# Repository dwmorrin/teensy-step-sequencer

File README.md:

# Teensy Step Sequencer

This project implements a hardware-based step sequencer using the Teensy 4.1 microcontroller. It utilizes the Teensy's onboard USB Host capabilities to accept input from standard USB keyboards, alongside a custom 32-switch diode matrix for tactile control.

## Gallery

### Version 1 first build

### Prototype

### Hardware Renders

|                         Main Board                         |                         Switchplate                         |
| :-----------------------------------------------------: | :-------------------------------------------------------: |
|  |  |

## System Overview

The application is designed as a standalone, embedded instrument. It functions as an **8-track** step sequencer with support for **96 PPQN high-resolution timing**, pattern chaining (Song Mode), **per-track swing**, real-time performance triggers, and visual feedback via an I2C OLED display with scrolling track views.

### Hardware Dependencies

- **Microcontroller:** Teensy 4.1 (Selected for native USB Host and RAM capacity).
- **Display:** - 1.3" SH1106 OLED (I2C) for the graphical interface.
  - 16x LEDs driven by 74HC595 Shift Registers for step visualization.
- **Input:** - Standard USB HID Keyboard (via USB Host).
  - 4x8 Diode Matrix Keyboard (32 switches).
  - 2x Analog Potentiometers (Tempo and Parameter control).
- **Output:** **8x** 5V Logic Triggers (GPIO).

## Software Architecture

The codebase adopts a modular architecture separating data, presentation, and hardware control. The source code located in `src/` is organized into the following domains:

- **Model** (`src/Model/`)
  This directory contains the core logic and data structures. It serves as the single source of truth for the application, managing the Pattern Pool, the Playlist (Song Mode), Swing parameters, and the Undo buffer. The Model is decoupled from hardware; it does not know if it is being driven by a clock or edited by a keyboard.

- **View** (`src/View/`)
  This directory handles all visual output.
  - `DisplayManager`: Observes the Model and renders the interface (Grid, Transport, Headers) to the OLED. It handles **viewport scrolling** to display 8 tracks on a 4-track height screen.
  - `StepLeds`: Manages the 16-step LED array via SPI shift registers.
    The view layer includes internal throttling logic to maintain a consistent frame rate without blocking the audio/timing threads.

- **Controller** (`src/Controller/`)
  This directory manages user input and state routing. The `UIManager` aggregates inputs from multiple hardware sources:
  - **USB Keyboard:** Handled via the Teensy USBHost_t36 library.
  - **Matrix:** Handled by `KeyMatrix`, a custom driver for scanning the 4x8 diode array.
  - **Analog:** Handled by `AnalogInput`, which provides hysteresis and signal smoothing for potentiometers.

  Inputs are translated into abstract `InputCommands` (e.g., `CMD_TRANSPORT_TOGGLE`), decoupling the physical control method from the internal application logic.

- **Engine** (`src/Engine/`)
  This directory handles real-time operations.
  - `ClockEngine`: A **96 PPQN** (Pulses Per Quarter Note) interrupt-driven engine. It calculates micro-timing for **Swing** and groove effects, offering 24 "ticks" per 16th-note step.
  - `OutputDriver`: Abstraction layer for the physical hardware. It converts track bitmasks into GPIO signals using high-precision interrupt timers.

- **Configuration** (`src/Config.h`)
  A global header file defining build-time constraints, including track count, pattern limits, pin mappings, and signal polarity.

## Expansion Guidelines

The system is designed to be extensible. Developers looking to expand functionality should consider the following architectural patterns:

### Persistence (SD Card Storage)

Current pattern data is stored in volatile RAM and is lost upon power cycle. The Teensy 4.1 includes a native micro-SD card slot. Future development should implement a `PersistenceManager` class. This component should:

1.  Serialize the `SequencerModel` data structures (Pattern Pool and Playlist) into a binary or JSON format.
2.  Write to the SD card using the standard Arduino SD library.
3.  Interface with the `UIManager` to allow loading and saving of projects.

## Timing Calculation

The system timing is based on a standard 4/4 time signature where a "beat" represents a quarter note. 

The engine runs at **96 PPQN** resolution. The interval $T$ (milliseconds per tick) is calculated as:

$$T = \frac{60,000}{BPM \times 96}$$

For a standard trigger pulse width of 15ms, the system manages overlapping triggers via a pulse-counter in the interrupt service routine.

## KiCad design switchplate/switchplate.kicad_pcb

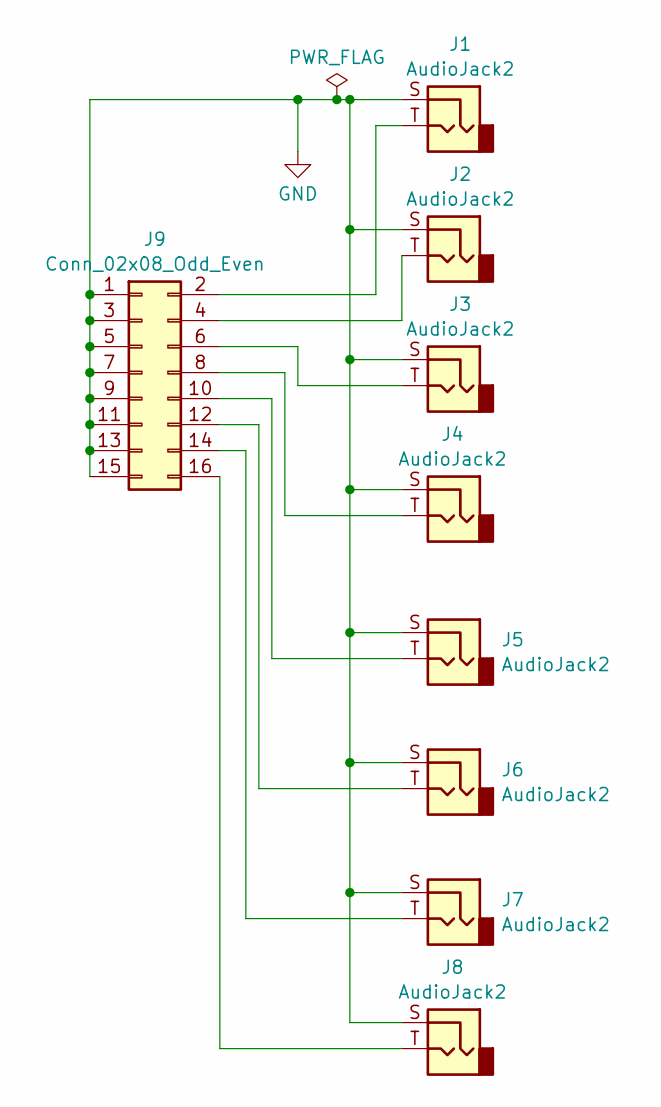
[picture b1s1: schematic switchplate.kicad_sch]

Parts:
J1, J2, J3, J4, J5, J6, J7, J8: AudioJack2; Jack_3.5mm_CUI_SJ1-3523N_Horizontal; MPN SJ1-3523N
J9: Conn_02x08_Odd_Even; PinHeader_2x08_P2.54mm_Vertical; MPN TSW-108-14-T-D

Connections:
GND: J1.S, J2.S, J3.S, J4.S, J5.S, J6.S, J7.S, J8.S, J9.1, J9.3, J9.5, J9.7, J9.9, J9.11, J9.13, J9.15
unnamed: J1.T, J9.2
unnamed: J2.T, J9.4
unnamed: J3.T, J9.6
unnamed: J4.T, J9.8
unnamed: J5.T, J9.10
unnamed: J6.T, J9.12
unnamed: J7.T, J9.14
unnamed: J8.T, J9.16

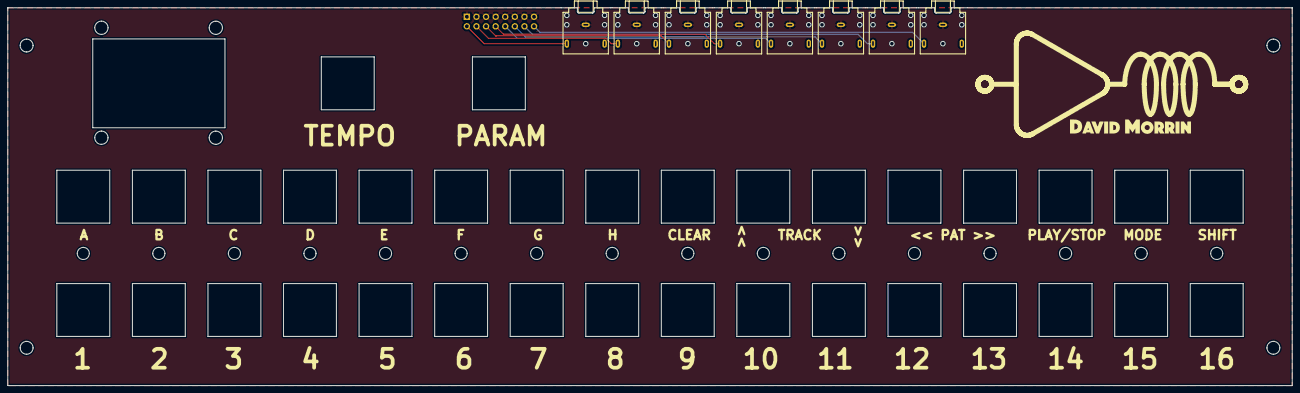
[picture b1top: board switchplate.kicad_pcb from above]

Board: 2 copper layers, 340.0 x 100.0 mm, 9 parts (1 on the bottom side), 9 nets.

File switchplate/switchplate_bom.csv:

Reference	Qty	Value	DNP	Exclude from BOM	Exclude from Board	Footprint	Datasheet	MPN
J1,J2,J3,J4,J5,J6,J7,J8	8	AudioJack2				Connector_Audio:Jack_3.5mm_CUI_SJ1-3523N_Horizontal	https://www.mouser.com/datasheet/3/6118/1/sj1_352xn.pdf	SJ1-3523N
J9	1	Conn_02x08_Odd_Even				Connector_PinHeader_2.54mm:PinHeader_2x08_P2.54mm_Vertical	https://suddendocs.samtec.com/productspecs/tsw-sxx.pdf	TSW-108-14-T-D

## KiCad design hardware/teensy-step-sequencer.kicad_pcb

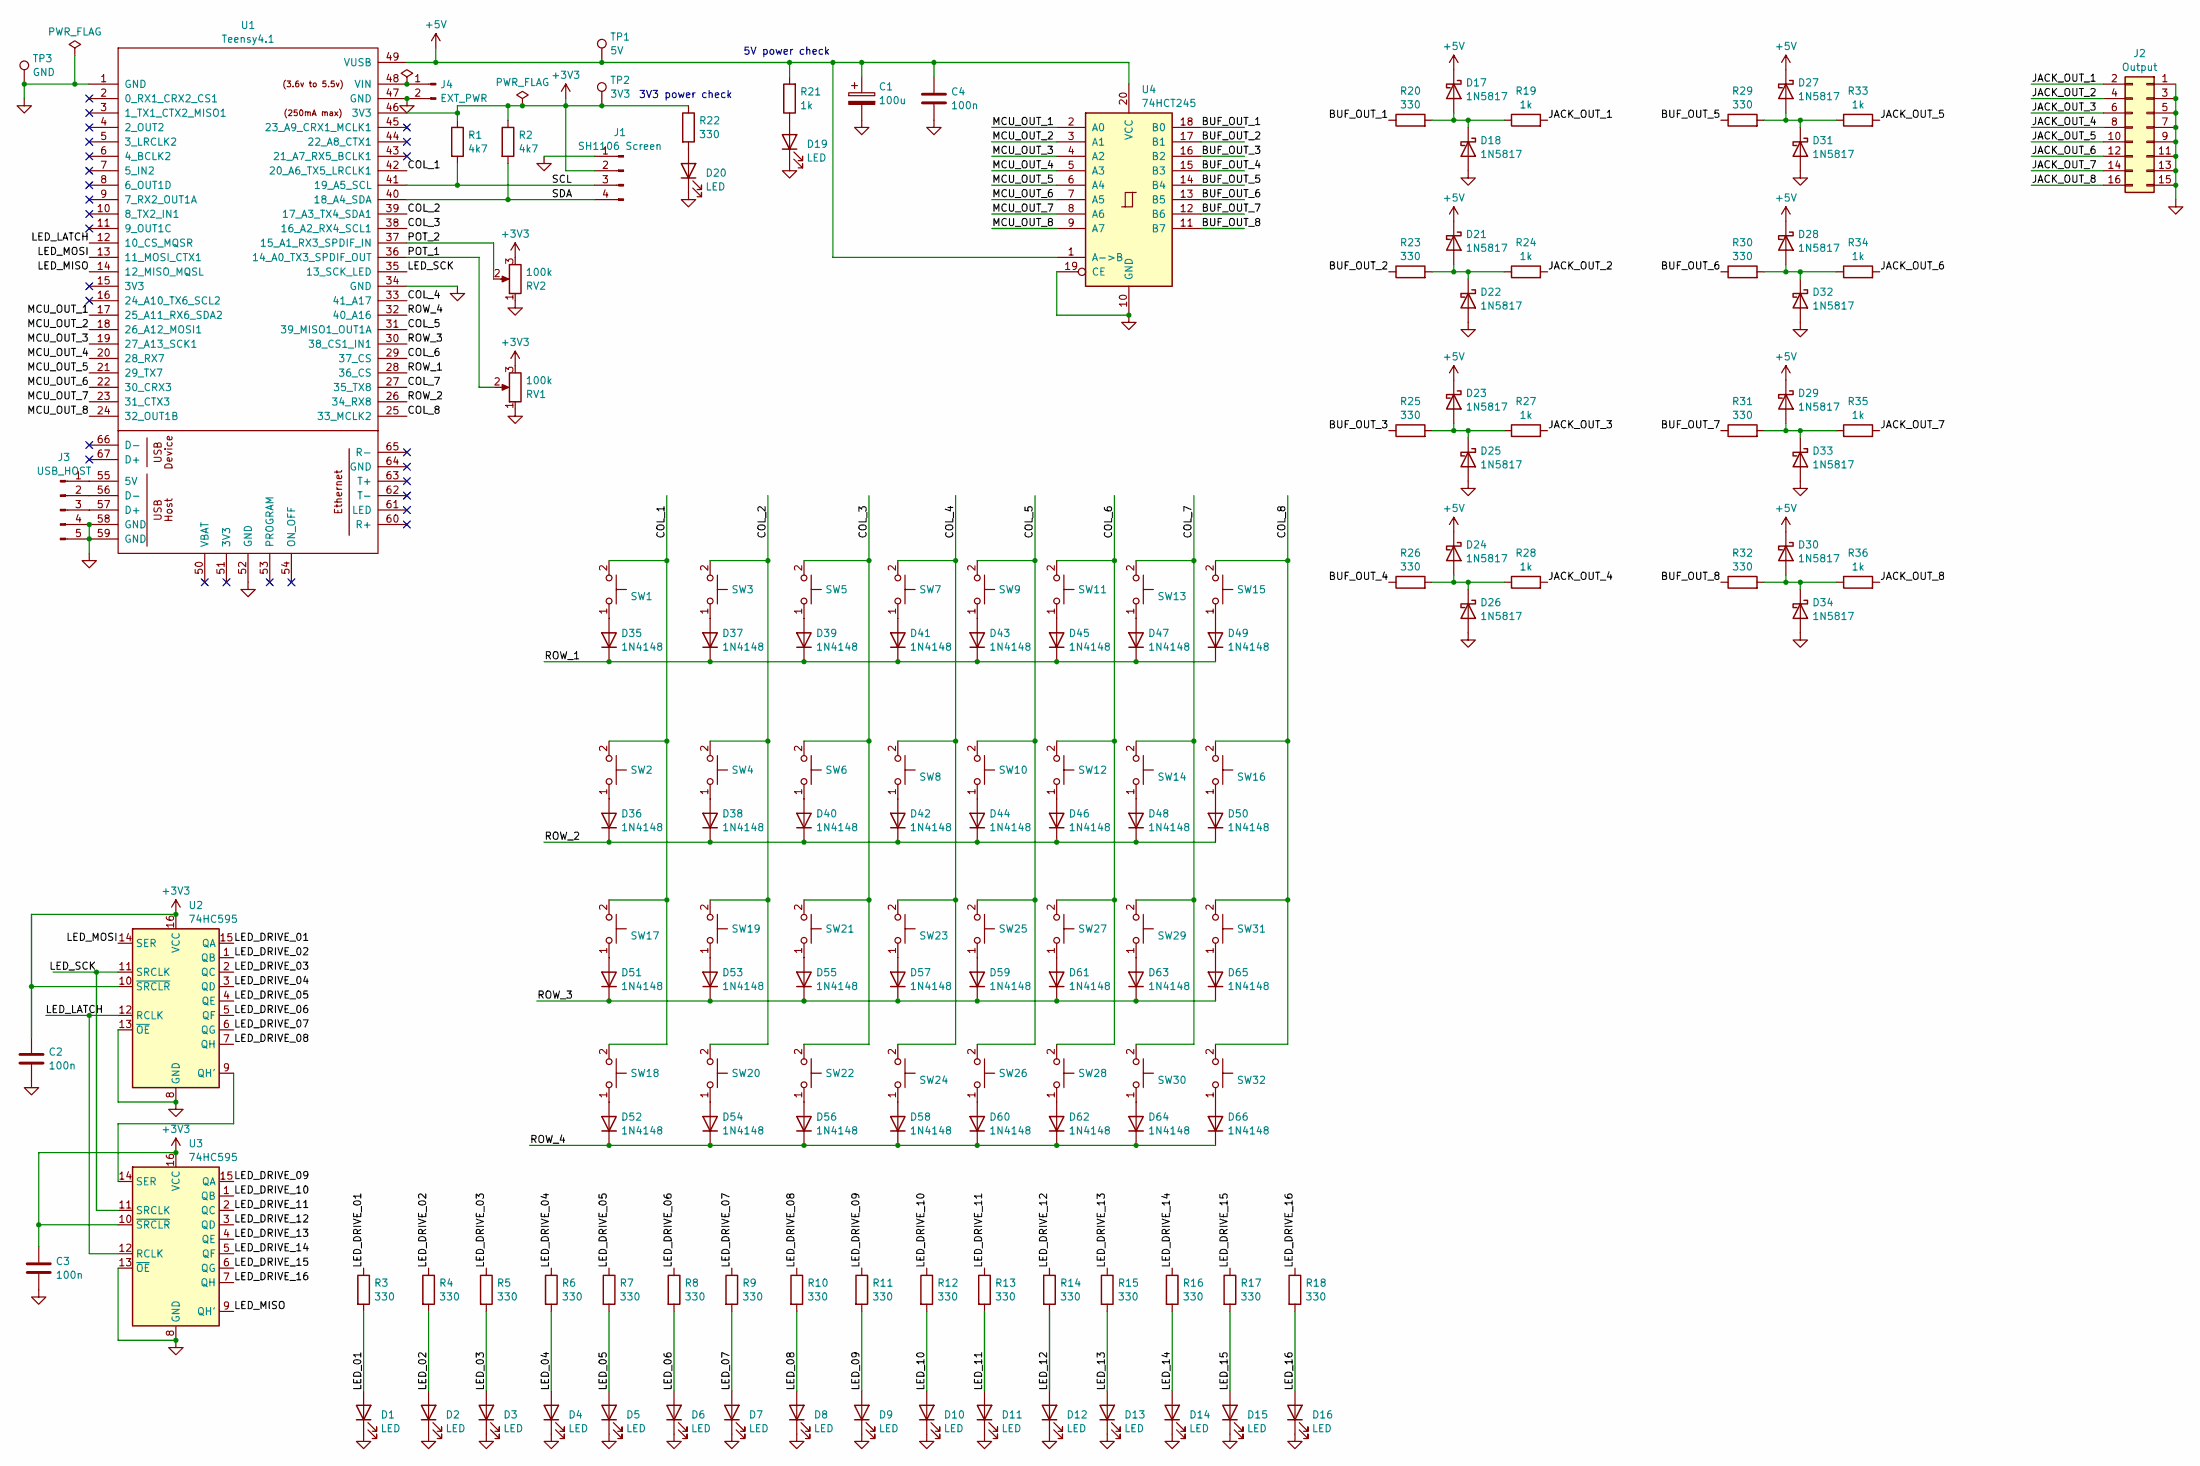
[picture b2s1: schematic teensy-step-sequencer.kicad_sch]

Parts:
C1: 100u; CP_Radial_D5.0mm_P2.50mm
C2, C3, C4: 100n; C_Disc_D5.0mm_W2.5mm_P2.50mm
D1, D2, D3, D4, D5, D6, D7, D8, D9, D10, D11, D12, D13, D14, D15, D16, D19, D20: LED; LED_D3.0mm
D17, D18, D21, D22, D23, D24, D25, D26, D27, D28, D29, D30, D31, D32, D33, D34: 1N5817; D_DO-15_P10.16mm_Horizontal
D35, D36, D37, D38, D39, D40, D41, D42, D43, D44, D45, D46, D47, D48, D49, D50, D51, D52, D53, D54, D55, D56, D57, D58, D59, D60, D61, D62, D63, D64, D65, D66: 1N4148; D_DO-35_SOD27_P7.62mm_Horizontal
J1: SH1106 Screen; PinHeader_1x04_P2.54mm_Vertical
J2: Output; PinHeader_2x08_P2.54mm_Vertical
J3: USB_HOST; PinHeader_1x05_P2.54mm_Vertical
J4: EXT_PWR; PinHeader_1x02_P2.54mm_Vertical
R1, R2: 4k7; R_Axial_DIN0207_L6.3mm_D2.5mm_P10.16mm_Horizontal
R3, R4, R5, R6, R7, R8, R9, R10, R11, R12, R13, R14, R15, R16, R17, R18, R20, R22, R23, R25, R26, R29, R30, R31, R32: 330; R_Axial_DIN0207_L6.3mm_D2.5mm_P10.16mm_Horizontal
R19, R21, R24, R27, R28, R33, R34, R35, R36: 1k; R_Axial_DIN0207_L6.3mm_D2.5mm_P10.16mm_Horizontal
RV1, RV2: 100k; Potentiometer_Bourns_PTV09A-1_Single_Vertical
SW1, SW2, SW3, SW4, SW5, SW6, SW7, SW8, SW9, SW10, SW11, SW12, SW13, SW14, SW15, SW16, SW17, SW18, SW19, SW20, SW21, SW22, SW23, SW24, SW25, SW26, SW27, SW28, SW29, SW30, SW31, SW32: CherryMX; CherryMX_1.00u
TP1: 5V; TestPoint_Keystone_5000-5004_Miniature
TP2: 3V3; TestPoint_Keystone_5000-5004_Miniature
TP3: GND; TestPoint_Keystone_5000-5004_Miniature
U1: Teensy4.1; Teensy41
U2, U3: 74HC595; DIP-16_W7.62mm
U4: 74HCT245; DIP-20_W7.62mm

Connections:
+3V3: C2.1, C3.1, J1.2, R1.1, R2.1, R22.1, RV1.3, RV2.3, TP2.1, U1.46 (3V3), U2.10 (~SRCLR), U2.16 (VCC), U3.10 (~SRCLR), U3.16 (VCC)
+5V: C1.1, C4.1, D17.1 (K), D21.1 (K), D23.1 (K), D24.1 (K), D27.1 (K), D28.1 (K), D29.1 (K), D30.1 (K), R21.2, TP1.1, U1.49 (VUSB), U4.1 (A->B), U4.20 (VCC)
/BUF_OUT_1: R20.1, U4.18 (B0)
/BUF_OUT_2: R23.1, U4.17 (B1)
/BUF_OUT_3: R25.1, U4.16 (B2)
/BUF_OUT_4: R26.1, U4.15 (B3)
/BUF_OUT_5: R29.1, U4.14 (B4)
/BUF_OUT_6: R30.1, U4.13 (B5)
/BUF_OUT_7: R31.1, U4.12 (B6)
/BUF_OUT_8: R32.1, U4.11 (B7)
/COL_1: SW1.2, SW2.2, SW17.2, SW18.2, U1.42 (20_A6_TX5_LRCLK1)
/COL_2: SW3.2, SW4.2, SW19.2, SW20.2, U1.39 (17_A3_TX4_SDA1)
/COL_3: SW5.2, SW6.2, SW21.2, SW22.2, U1.38 (16_A2_RX4_SCL1)
/COL_4: SW7.2, SW8.2, SW23.2, SW24.2, U1.33 (41_A17)
/COL_5: SW9.2, SW10.2, SW25.2, SW26.2, U1.31 (39_MISO1_OUT1A)
/COL_6: SW11.2, SW12.2, SW27.2, SW28.2, U1.29 (37_CS)
/COL_7: SW13.2, SW14.2, SW29.2, SW30.2, U1.27 (35_TX8)
/COL_8: SW15.2, SW16.2, SW31.2, SW32.2, U1.25 (33_MCLK2)
/JACK_OUT_1: J2.2, R19.2
/JACK_OUT_2: J2.4, R24.2
/JACK_OUT_3: J2.6, R27.2
/JACK_OUT_4: J2.8, R28.2
/JACK_OUT_5: J2.10, R33.2
/JACK_OUT_6: J2.12, R34.2
/JACK_OUT_7: J2.14, R35.2
/JACK_OUT_8: J2.16, R36.2
/LED_01: D1.2 (A), R3.2
/LED_02: D2.2 (A), R4.2
/LED_03: D3.2 (A), R5.2
/LED_04: D4.2 (A), R6.2
/LED_05: D5.2 (A), R7.2
/LED_06: D6.2 (A), R8.2
/LED_07: D7.2 (A), R9.2
/LED_08: D8.2 (A), R10.2
/LED_09: D9.2 (A), R11.2
/LED_10: D10.2 (A), R12.2
/LED_11: D11.2 (A), R13.2
/LED_12: D12.2 (A), R14.2
/LED_13: D13.2 (A), R15.2
/LED_14: D14.2 (A), R16.2
/LED_15: D15.2 (A), R17.2
/LED_16: D16.2 (A), R18.2
/LED_DRIVE_01: R3.1, U2.15 (QA)
/LED_DRIVE_02: R4.1, U2.1 (QB)
/LED_DRIVE_03: R5.1, U2.2 (QC)
/LED_DRIVE_04: R6.1, U2.3 (QD)
/LED_DRIVE_05: R7.1, U2.4 (QE)
/LED_DRIVE_06: R8.1, U2.5 (QF)
/LED_DRIVE_07: R9.1, U2.6 (QG)
/LED_DRIVE_08: R10.1, U2.7 (QH)
/LED_DRIVE_09: R11.1, U3.15 (QA)
/LED_DRIVE_10: R12.1, U3.1 (QB)
/LED_DRIVE_11: R13.1, U3.2 (QC)
/LED_DRIVE_12: R14.1, U3.3 (QD)
/LED_DRIVE_13: R15.1, U3.4 (QE)
/LED_DRIVE_14: R16.1, U3.5 (QF)
/LED_DRIVE_15: R17.1, U3.6 (QG)
/LED_DRIVE_16: R18.1, U3.7 (QH)
/LED_LATCH: U1.12 (10_CS_MQSR), U2.12 (RCLK), U3.12 (RCLK)
/LED_MISO: U1.14 (12_MISO_MQSL), U3.9 (QH')
/LED_MOSI: U1.13 (11_MOSI_CTX1), U2.14 (SER)
/LED_SCK: U1.35 (13_SCK_LED), U2.11 (SRCLK), U3.11 (SRCLK)
/MCU_OUT_1: U1.17 (25_A11_RX6_SDA2), U4.2 (A0)
/MCU_OUT_2: U1.18 (26_A12_MOSI1), U4.3 (A1)
/MCU_OUT_3: U1.19 (27_A13_SCK1), U4.4 (A2)
/MCU_OUT_4: U1.20 (28_RX7), U4.5 (A3)
/MCU_OUT_5: U1.21 (29_TX7), U4.6 (A4)
/MCU_OUT_6: U1.22 (30_CRX3), U4.7 (A5)
/MCU_OUT_7: U1.23 (31_CTX3), U4.8 (A6)
/MCU_OUT_8: U1.24 (32_OUT1B), U4.9 (A7)
/POT_1: RV1.2, U1.36 (14_A0_TX3_SPDIF_OUT)
/POT_2: RV2.2, U1.37 (15_A1_RX3_SPDIF_IN)
/ROW_1: D35.1 (K), D37.1 (K), D39.1 (K), D41.1 (K), D43.1 (K), D45.1 (K), D47.1 (K), D49.1 (K), U1.28 (36_CS)
/ROW_2: D36.1 (K), D38.1 (K), D40.1 (K), D42.1 (K), D44.1 (K), D46.1 (K), D48.1 (K), D50.1 (K), U1.26 (34_RX8)
/ROW_3: D51.1 (K), D53.1 (K), D55.1 (K), D57.1 (K), D59.1 (K), D61.1 (K), D63.1 (K), D65.1 (K), U1.30 (38_CS1_IN1)
/ROW_4: D52.1 (K), D54.1 (K), D56.1 (K), D58.1 (K), D60.1 (K), D62.1 (K), D64.1 (K), D66.1 (K), U1.32 (40_A16)
/SCL: J1.3, R1.2, U1.41 (19_A5_SCL)
/SDA: J1.4, R2.2, U1.40 (18_A4_SDA)
GND: C1.2, C2.2, C3.2, C4.2, D1.1 (K), D2.1 (K), D3.1 (K), D4.1 (K), D5.1 (K), D6.1 (K), D7.1 (K), D8.1 (K), D9.1 (K), D10.1 (K), D11.1 (K), D12.1 (K), D13.1 (K), D14.1 (K), D15.1 (K), D16.1 (K), D18.2 (A), D19.1 (K), D20.1 (K), D22.2 (A), D25.2 (A), D26.2 (A), D31.2 (A), D32.2 (A), D33.2 (A), D34.2 (A), J1.1, J2.1, J2.3, J2.5, J2.7, J2.9, J2.11, J2.13, J2.15, J3.4, J3.5, J4.2, RV1.1, RV2.1, TP3.1, U1.1 (GND), U1.34 (GND), U1.47 (GND), U1.52 (GND), U1.58 (GND), U1.59 (GND), U2.8 (GND), U2.13 (~OE), U3.8 (GND), U3.13 (~OE), U4.10 (GND), U4.19 (CE)
unnamed: D17.2 (A), D18.1 (K), R19.1, R20.2
unnamed: D19.2 (A), R21.1
unnamed: D20.2 (A), R22.2
unnamed: D21.2 (A), D22.1 (K), R23.2, R24.1
unnamed: D23.2 (A), D25.1 (K), R25.2, R27.1
unnamed: D24.2 (A), D26.1 (K), R26.2, R28.1
unnamed: D27.2 (A), D31.1 (K), R29.2, R33.1
unnamed: D28.2 (A), D32.1 (K), R30.2, R34.1
unnamed: D29.2 (A), D33.1 (K), R31.2, R35.1
unnamed: D30.2 (A), D34.1 (K), R32.2, R36.1
unnamed: D35.2 (A), SW1.1
unnamed: D36.2 (A), SW2.1
unnamed: D37.2 (A), SW3.1
unnamed: D38.2 (A), SW4.1
unnamed: D39.2 (A), SW5.1
unnamed: D40.2 (A), SW6.1
unnamed: D41.2 (A), SW7.1
unnamed: D42.2 (A), SW8.1
unnamed: D43.2 (A), SW9.1
unnamed: D44.2 (A), SW10.1
unnamed: D45.2 (A), SW11.1
unnamed: D46.2 (A), SW12.1
unnamed: D47.2 (A), SW13.1
unnamed: D48.2 (A), SW14.1
unnamed: D49.2 (A), SW15.1
unnamed: D50.2 (A), SW16.1
unnamed: D51.2 (A), SW17.1
unnamed: D52.2 (A), SW18.1
unnamed: D53.2 (A), SW19.1
unnamed: D54.2 (A), SW20.1
unnamed: D55.2 (A), SW21.1
unnamed: D56.2 (A), SW22.1
unnamed: D57.2 (A), SW23.1
unnamed: D58.2 (A), SW24.1
unnamed: D59.2 (A), SW25.1
unnamed: D60.2 (A), SW26.1
unnamed: D61.2 (A), SW27.1
unnamed: D62.2 (A), SW28.1
unnamed: D63.2 (A), SW29.1
unnamed: D64.2 (A), SW30.1
unnamed: D65.2 (A), SW31.1
unnamed: D66.2 (A), SW32.1
unnamed: J3.1, U1.55 (5V)
unnamed: J3.2, U1.56 (D-)
unnamed: J3.3, U1.57 (D+)
unnamed: J4.1, U1.48 (VIN)
unnamed: U2.9 (QH'), U3.14 (SER)

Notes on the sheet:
5V power check
3V3 power check

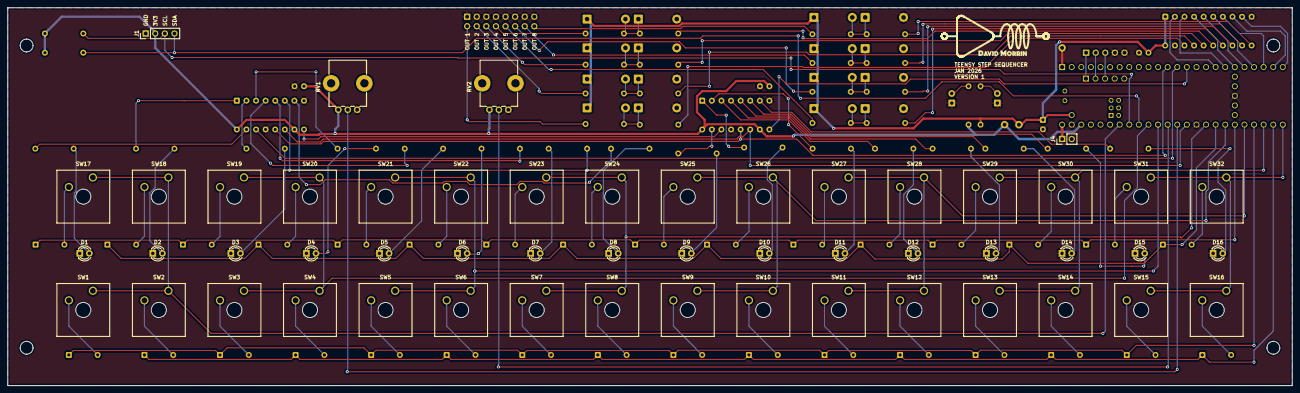
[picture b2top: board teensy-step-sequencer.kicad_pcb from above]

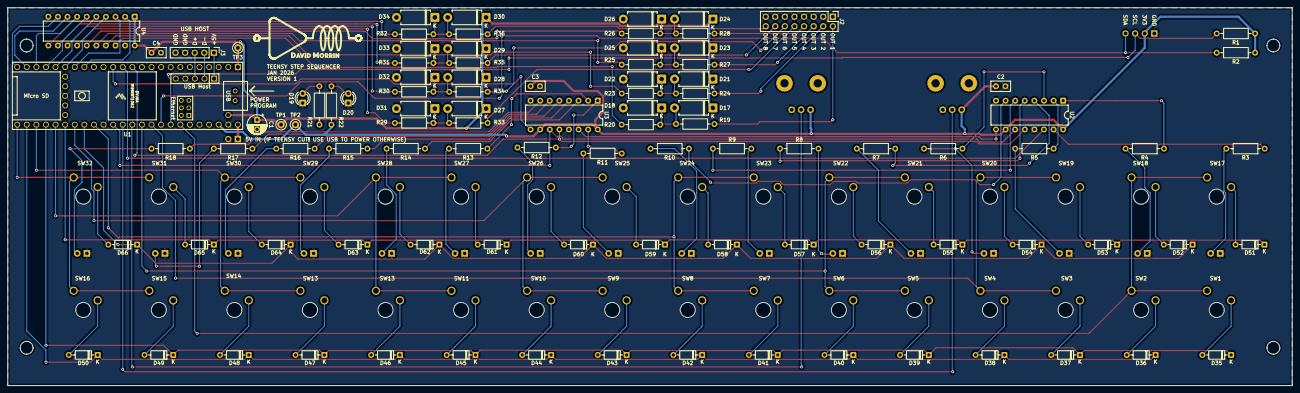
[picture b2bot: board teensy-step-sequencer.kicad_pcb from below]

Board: 2 copper layers, 340.0 x 100.0 mm, 151 parts (99 on the bottom side), 126 nets.

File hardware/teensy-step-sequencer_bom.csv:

Reference	Qty	Value	DNP	Exclude from BOM	Exclude from Board	Footprint	Datasheet
C1	1	100u				Capacitor_THT:CP_Radial_D5.0mm_P2.50mm	~
C2,C3,C4	3	100n				Capacitor_THT:C_Disc_D5.0mm_W2.5mm_P2.50mm	~
D1,D2,D3,D4,D5,D6,D7,D8,D9,D10,D11,D12,D13,D14,D15,D16,D19,D20	18	LED				LED_THT:LED_D3.0mm	~
D17,D18,D21,D22,D23,D24,D25,D26,D27,D28,D29,D30,D31,D32,D33,D34	16	1N5817				Diode_THT:D_DO-15_P10.16mm_Horizontal	http://www.vishay.com/docs/88525/1n5817.pdf
D35,D36,D37,D38,D39,D40,D41,D42,D43,D44,D45,D46,D47,D48,D49,D50,D51,D52,D53,D54,D55,D56,D57,D58,D59,D60,D61,D62,D63,D64,D65,D66	32	1N4148				Diode_THT:D_DO-35_SOD27_P7.62mm_Horizontal	~
J1	1	SH1106 Screen				Connector_PinHeader_2.54mm:PinHeader_1x04_P2.54mm_Vertical	~
J2	1	Output				Connector_PinHeader_2.54mm:PinHeader_2x08_P2.54mm_Vertical	~
J3	1	USB_HOST				Connector_PinHeader_2.54mm:PinHeader_1x05_P2.54mm_Vertical	~
J4	1	EXT_PWR				Connector_PinHeader_2.54mm:PinHeader_1x02_P2.54mm_Vertical	~
R1,R2	2	4k7				Resistor_THT:R_Axial_DIN0207_L6.3mm_D2.5mm_P10.16mm_Horizontal	~
R3,R4,R5,R6,R7,R8,R9,R10,R11,R12,R13,R14,R15,R16,R17,R18,R20,R22,R23,R25,R26,R29,R30,R31,R32	25	330				Resistor_THT:R_Axial_DIN0207_L6.3mm_D2.5mm_P10.16mm_Horizontal	~
R19,R21,R24,R27,R28,R33,R34,R35,R36	9	1k				Resistor_THT:R_Axial_DIN0207_L6.3mm_D2.5mm_P10.16mm_Horizontal	~
RV1,RV2	2	100k				Potentiometer_THT:Potentiometer_Bourns_PTV09A-1_Single_Vertical	~
SW1,SW2,SW3,SW4,SW5,SW6,SW7,SW8,SW9,SW10,SW11,SW12,SW13,SW14,SW15,SW16,SW17,SW18,SW19,SW20,SW21,SW22,SW23,SW24,SW25,SW26,SW27,SW28,SW29,SW30,SW31,SW32	32	CherryMX				CherryMX:CherryMX_1.00u	
TP1	1	5V				TestPoint:TestPoint_Keystone_5000-5004_Miniature	~
TP2	1	3V3				TestPoint:TestPoint_Keystone_5000-5004_Miniature	~
TP3	1	GND				TestPoint:TestPoint_Keystone_5000-5004_Miniature	~
U1	1	Teensy4.1				teensy:Teensy41	
U2,U3	2	74HC595				Package_DIP:DIP-16_W7.62mm	http://www.ti.com/lit/ds/symlink/sn74hc595.pdf
U4	1	74HCT245				Package_DIP:DIP-20_W7.62mm	http://www.ti.com/lit/gpn/sn74HC245

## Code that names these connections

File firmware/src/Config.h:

#pragma once

// --- SYSTEM LIMITS ---
#define NUM_TRACKS 8
#define NUM_STEPS 16
#define MAX_PATTERNS 64
#define MAX_SONG_LENGTH 128

// --- TIMING ---
#define PULSE_WIDTH_MS 15
#define DEFAULT_BPM 120

// --- HARDWARE MAPPING ---
const int OUTPUT_MAP[NUM_TRACKS] = {25, 26, 27, 28, 29, 30, 31, 32};

// --- INPUTS ---
const int PIN_POT_TEMPO = 14;
const int PIN_POT_PARAM = 15;

// KEY MATRIX PINS
// Rows (Active Low Output)
const int PIN_ROW_1 = 36;
const int PIN_ROW_2 = 34;
const int PIN_ROW_3 = 38;
const int PIN_ROW_4 = 40;

// Cols (Input Pullup)
const int PIN_COL_1 = 20;
const int PIN_COL_2 = 17;
const int PIN_COL_3 = 16;
const int PIN_COL_4 = 41;
const int PIN_COL_5 = 39;
const int PIN_COL_6 = 37;
const int PIN_COL_7 = 35;
const int PIN_COL_8 = 33;

// PCB REVISION NOTES
const bool POT_INVERT_POLARITY = true;

// --- OUTPUT POLARITY ---
#define TRIGGER_ON HIGH
#define TRIGGER_OFF LOW

// --- DISPLAY ---
#define TRACK_EDIT_STR "<"
#define TRACK_PERFORM_STR "*"

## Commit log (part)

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2026-01-24 feat: initial step sequencer design
2026-01-24 fix: triggers run on timer
2026-01-24 feat: adds global debug switch
2026-01-24 fix: allows LF or CR; DEL or BS
2026-01-25 feat: adds BPM control
2026-01-25 feat: adds song playlist editing
2026-01-25 fix: perform indicator
    TAB toggles between < and * track indicator with the latter meaning perform mode.
    Also compresses grid so the track indicator can be seen.
2026-01-25 feat: adds 'clear track' action
2026-01-25 feat: adds 'clear pattern' action
2026-01-25 fix: first beat sounds
2026-01-25 fix: clean up header display
2026-01-25 refactor: restructure repo for monorepo
    firmware/hardware split
2026-02-01 chore(root): consolidate gitignore rules and remove legacy config
2026-02-01 refactor(hardware): migrate main board to clean directory structure and consolidate libraries
2026-02-01 refactor(switchplate): migrate to monorepo structure and clean up libraries
2026-02-01 docs: centralize image assets and add gallery to README
2026-02-01 feat(view): integrate LED step display and hardware diagnostics
    - Add StepLeds driver for 74HC595 shift registers with MISO loopback
    - Add MODE_HARDWARE_TEST to SequencerModel and ClockEngine
    - Implement high-speed visual chaser in ClockEngine (timing override)
    - Update DisplayManager to sync LEDs with model and report self-test results
    - Bind 't' key in UIManager to toggle diagnostic mode
    Closes #2
2026-02-01 feat(controller): integrate analog potentiometers for tempo and parameter control
    - Add AnalogInput helper class with hysteresis filtering
    - Define PIN_POT_TEMPO (14) and PIN_POT_PARAM (15) in Config.h
    - Implement 'Last Action Wins' logic for BPM control (Pot vs Keyboard)
    - Add POT_INVERT_POLARITY flag to correct V1 PCB layout error
    - Tune Tempo Pot threshold to 4 ADC units (~1 BPM resolution)
    - Set Output Logic to Active High for hardware probing
2026-02-02 refactor(controller): implement command pattern for input handling
    - Introduce InputCommand enum to decouple input source from business logic
    - Refactor UIManager::handleKeyPress to act as a translator
    - Move core logic to UIManager::handleCommand
    - Fix mapping conflict between Step 14 and Playlist Delete
    - Restore Hardware Test toggle logic
    Closes #4
2026-02-02 fix(config): update output pin mapping for V1 PCB
    - Update OUTPUT_MAP to use pins 25-28 instead of 2-5 to match the V1 hardware layout.
2026-02-02 feat(hardware): implement diode matrix keyboard driver
    - Add KeyMatrix class to scan 4x8 switch matrix with open-drain logic
    - Map physical matrix switches to InputCommands (Steps, Tracks A-D, Transport)
    - Integrate KeyMatrix polling into UIManager::processInput
    - Implement modal confirmation logic using Step buttons (1-4=YES, 13-16=NO)
    - Update DisplayManager to show hardware-specific guidance for Clear actions
    Closes #5
2026-02-02 docs(readme): update documentation to reflect hardware and architecture changes
    - Add hardware dependency details for Matrix, Analog Pots, and LED array
    - Update Software Architecture to describe InputCommand pattern and new Controller modules
    - Refine Timing Calculation section with mathematical notation
2026-02-04 fix(controller): implement event buffer for simultaneous keypresses
    - Add Ring Buffer to KeyMatrix to store multiple events per frame
    - Decouple hardware scan (update) from event processing (getNextEvent)
    - Update UIManager to consume all buffered events each loop
    - Remove unused _mapToSwitchID declaration
    Closes #6
2026-02-04 fix(engine): move clock timing to hardware interrupt
    - Refactor ClockEngine to use IntervalTimer (1kHz ISR) for rock-solid timing
    - Eliminate tempo jitter caused by main loop/display latency
    - Simplify OutputDriver to be a stateless GPIO wrapper
    - Route manual UI triggers through ClockEngine to ensure correct pulse widths
    - Update initialization order in main.cpp to prevent startup glitches
    closes #10
2026-02-04 feat(ux): implement enhanced song mode workflow
    - Implement Song Mode input layer with Bank Selection (Shift+1-4) and Direct Pattern Assignment
    - Add Playlist Editing commands: Insert Before/After (Shift+Arrows) and Delete Slot (Clear)
    - Update DisplayManager LED logic to show Playhead Chaser when playing and Pattern ID when stopped
    - Map Param Pot to fine-tune Pattern ID selection in Song Mode
2026-02-04 fix(engine): ensure step 1 triggers immediately on playback start
    - Add _isFirstStep flag to ClockEngine to bypass advanceStep() on the initial tick
    - Corrects regression where the first step was skipped because the counter advanced before firing
2026-02-04 feat(engine): implement launch quantization and transition logic
    - Add Quantization Modes (1 Bar, 1/4, 1/8, Instant) to SequencerModel
    - Update ClockEngine to defer pattern changes until the quantization interval is met
    - Add 'Shift + Play' menu in UIManager to select quantization mode
    - Update DisplayManager to visualize pending transitions (blinking pattern ID)
    - Decouple 'View' pattern from 'Playing' pattern to allow queuing
2026-02-04 refactor(ux): swap Mode button behavior
    - Map MODE button to toggle Song/Loop Mode (CMD_SONG_MODE_TOGGLE)
    - Map SHIFT+MODE to toggle Edit/Perform Mode (CMD_MODE_TOGGLE)
    - Aligns hardware workflow with user preference for frequent Song Mode access
2026-02-04 feat(engine): implement 96 PPQN timing and per-track swing
    - Upgrade ClockEngine to 96 PPQN resolution (approx 2kHz ISR) for high-precision timing
    - Implement per-track, per-pattern Swing parameter (0-100%) in SequencerModel
    - Add tick-based trigger logic to delay off-beat steps based on swing amount
    - Map Shift+ParamPot in UIManager to control swing for the active track
    - Add visual feedback: transient value overlay and rhythmic grid displacement in DisplayManager
    Closes #1
2026-02-04 feat(hardware): expand to 8 tracks with scrolling UI
    - Increase NUM_TRACKS to 8 and update OUTPUT_MAP in Config.h
    - Update OutputDriver to initialize and trigger 8 pins
    - Remap Matrix inputs: Buttons A-H now select Tracks 1-8
    - Move UNDO command to SHIFT + H (formerly just H)
    - Implement scrolling grid in DisplayManager to view 8 tracks on a 4-track screen
    - Add visual track labels (A-H) in the right gutter for orientation
2026-02-04 docs: add v1.0.0 reference manual
2026-02-04 docs: add photos of v1.0 hardware build
